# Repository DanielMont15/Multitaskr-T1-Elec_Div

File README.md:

## Multitaskr-T1-Elec_Div
# Electronics Division  
ECAD and documentation repository for everything electronics related to Rotational &amp; Controlled Mechanism and transmission system for camera scanner project.

# Abstract
Among the services offered by Multitaskr, a 3D manual scanning of rooms with a camera is performed. With the purpose of improving processes, the automation of this process is proposed by developing a mobile and foldable platform that allows modifying the Pitch and Yaw position (in a range of 360 and -45 to 45, respectively) of the camera via a robotic system with 2 degrees of freedom.

The development considers the use of SCRUM methodology to keep track of the proposed objectives and detected failures; CAD and ECAD software (SolidWorks and Eagle); MATLAB for the design and tuning of the controller; TEC laboratories and other related facilities; as well as testing the system to identify areas of opportunity.

In order to achieve this goal, the process will last 10 weeks and will be divided into areas (Mechanics, Electronics, Control and Manufacturing) with the involvement of 8th semester students in Mechatronics with relevant experience in these areas. The testing phase is intended to ensure the delivery of a product according to the specifications.  

A functional prototype is expected to be delivered with the requirements established in the design process; as well as an "Engineering Manual" with CAD models, research processes, schematics, codes and operation guidelines along with the tests and areas of opportunity identified. 

It has been identified that the system can improve the accuracy and efficiency of the process, benefiting Multitaskr operationally and providing its clients with greater value in the services acquired.

# Objective of this repository
To track and mantain in a single platform all related documents in order to be able to replicate the project if needed. Expect to find:
* Entries to the Engineering Manual on the electronics subdivision and updates to said entries.
* ECAD files of the desgined circuits
* Diagrams/Drawings

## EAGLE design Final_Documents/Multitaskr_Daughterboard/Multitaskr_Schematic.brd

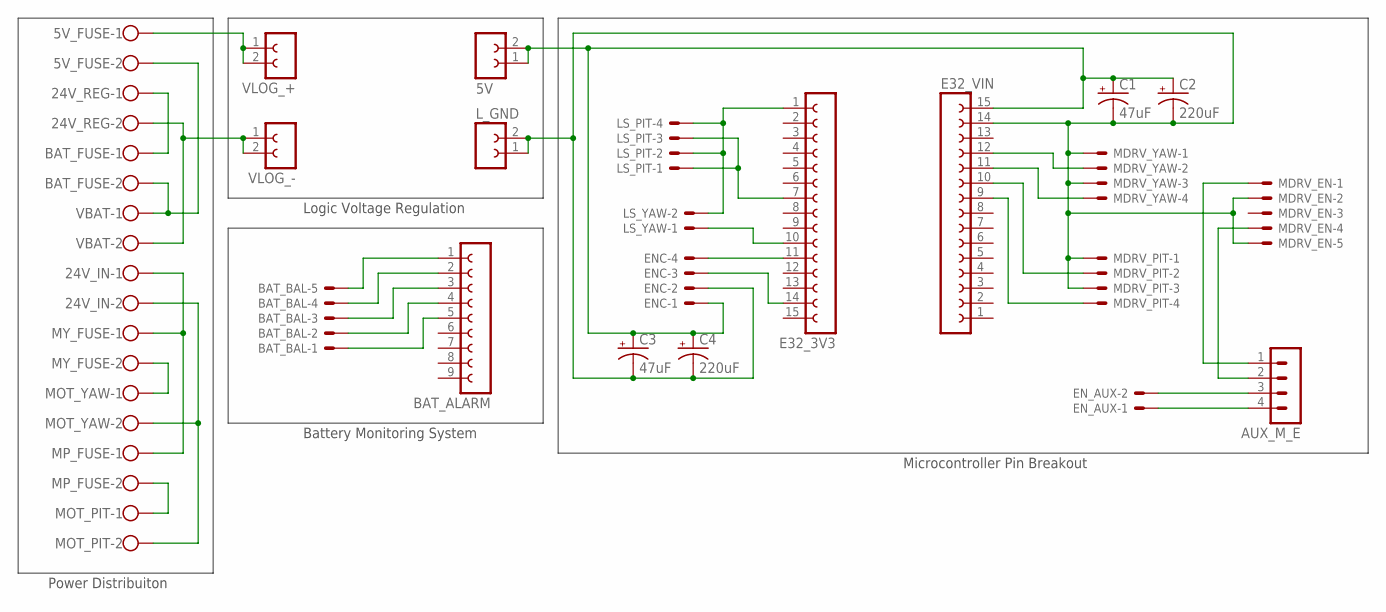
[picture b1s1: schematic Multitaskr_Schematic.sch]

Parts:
5V: FE05-1
5V_FUSE, 24V_IN, 24V_REG: SCREW_TERMINAL; FP_ST
AUX_M_E: MA04-1
BAT_ALARM: FE09-1; FE09
BAT_BAL: JST-XH-05-PIN-ROUND-PAD; JST-XH-05-PACKAGE-ROUND-PAD
BAT_FUSE: SCREW_TERMINAL; FP_ST
C1: 47uF; E2,5-7
C2: 220uF; E2,5RE
C3: 47uF; E2,5RE
C4: 220uF; E2,5-7
E32_3V3, E32_VIN: FE15-1; FE15
ENC: JST-XH-04-PIN-ROUND-PAD; JST-XH-04-PACKAGE-ROUND-PAD
EN_AUX: JST-XH-02-PIN-ROUND-PAD; JST-XH-02-PACKAGE-ROUND-PAD
LS_PIT: JST-XH-04-PIN-ROUND-PAD; JST-XH-04-PACKAGE-ROUND-PAD
LS_YAW: JST-XH-02-PIN-ROUND-PAD; JST-XH-02-PACKAGE-ROUND-PAD
L_GND: FE05-1
MDRV_EN: JST-XH-05-PIN-ROUND-PAD; JST-XH-05-PACKAGE-ROUND-PAD
MDRV_PIT: JST-XH-04-PIN-ROUND-PAD; JST-XH-04-PACKAGE-ROUND-PAD
MDRV_YAW: JST-XH-04-PIN-ROUND-PAD; JST-XH-04-PACKAGE-ROUND-PAD
MOT_PIT: SCREW_TERMINAL; FP_ST
MOT_YAW: SCREW_TERMINAL; FP_ST
MP_FUSE: SCREW_TERMINAL; FP_ST
MY_FUSE: SCREW_TERMINAL; FP_ST
VBAT: SCREW_TERMINAL; FP_ST
VLOG_+: FE05-1
VLOG_-: FE05-1

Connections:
1S: BAT_ALARM.2, BAT_BAL.4
2S: BAT_ALARM.3, BAT_BAL.3
3S: BAT_ALARM.4, BAT_BAL.2
3V3: E32_3V3.1, LS_PIT.2, LS_PIT.4, LS_YAW.2
4S: BAT_ALARM.5, BAT_BAL.1
5V: 5V.1, 5V.2, C1.+, C2.+, C3.+, C4.+, E32_VIN.15, ENC.1
24V: 24V_IN.1, MP_FUSE.1, MY_FUSE.1
-S: BAT_ALARM.1, BAT_BAL.5
BAT+: 5V_FUSE.2, BAT_FUSE.2, VBAT.1
BAT-: 24V_REG.2, VBAT.2, VLOG_-.1, VLOG_-.2
ENA_MOT_PIT: AUX_M_E.1, MDRV_EN.1
ENA_MOT_Y: AUX_M_E.2, MDRV_EN.4
EN_DIR: AUX_M_E.4, EN_AUX.1
EN_PGO: AUX_M_E.3, EN_AUX.2
ESP_SCL: E32_3V3.14, ENC.3
ESP_SDA: E32_3V3.11, ENC.4
FUSE_P: MOT_PIT.1, MP_FUSE.2
FUSE_REG: 24V_REG.1, BAT_FUSE.1
FUSE_Y: MOT_YAW.1, MY_FUSE.2
LS_PITCH: E32_3V3.7, LS_PIT.1, LS_PIT.3
LS_YAW: E32_3V3.10, LS_YAW.1
LV+: 5V_FUSE.1, VLOG_+.1, VLOG_+.2
L_GND: C1.-, C2.-, C3.-, C4.-, E32_VIN.14, ENC.2, L_GND.1, L_GND.2, MDRV_EN.2, MDRV_EN.5, MDRV_PIT.1, MDRV_PIT.3, MDRV_YAW.1, MDRV_YAW.3
M_GND: 24V_IN.2, MOT_PIT.2, MOT_YAW.2
PITCH_DIR: E32_VIN.10, MDRV_PIT.2
PITCH_PUL: E32_VIN.9, MDRV_PIT.4
YAW_DIR: E32_VIN.12, MDRV_YAW.2
YAW_PUL: E32_VIN.11, MDRV_YAW.4

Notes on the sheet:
Power Distribuiton
Logic Voltage Regulation
Battery Monitoring System
Microcontroller Pin Breakout

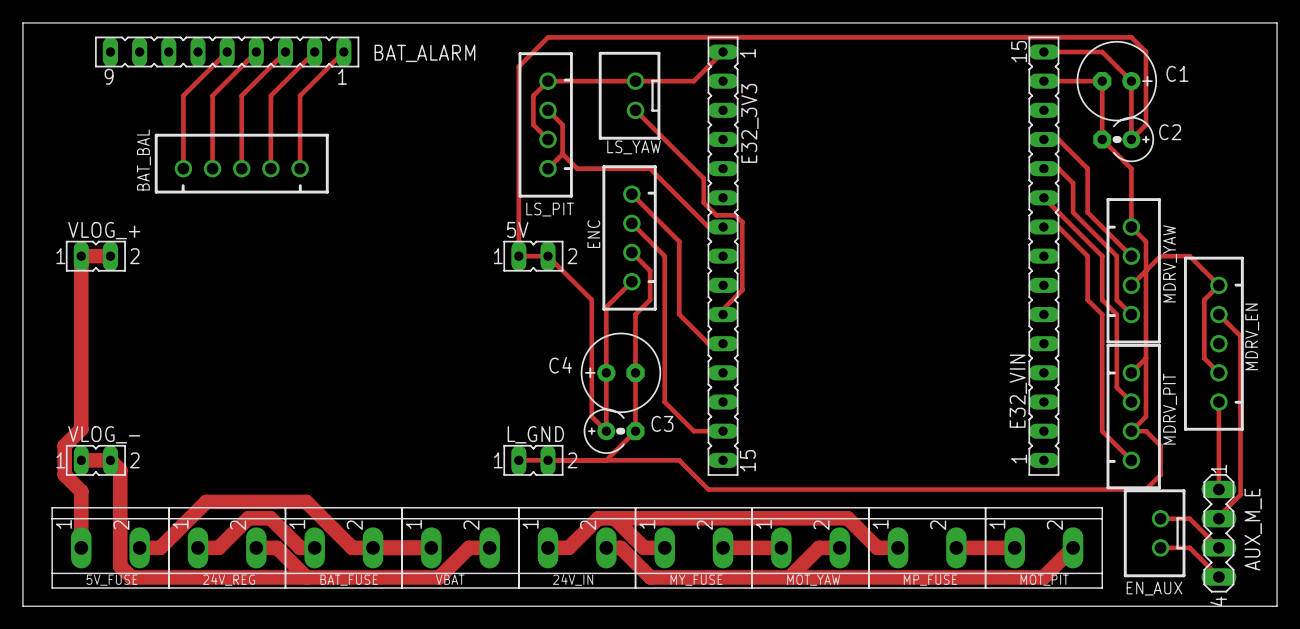
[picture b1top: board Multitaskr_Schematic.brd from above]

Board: 2 copper layers, 109.2 x 50.8 mm, 29 parts (0 on the bottom side), 28 nets.

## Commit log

2023-05-06 Updated README.md to describe project
2023-05-06 Added Log Books to git repository
2023-05-06 Added directory for Engineering Manual Entries
2023-05-06 Delete Engineering_Manual directory
    Fix Errors while uploading
2023-05-06 Created directory for Engineering entries; uploaded EM_ELEC-Selección_Fuente_Poder
2023-05-06 Added entry EM_ELEC-Selección_Microcontrolador
2023-05-06 Added first researchs documents of the project
2023-05-06 Added Actividad 2.1. Definición de objetivos, justificación y resultados esperados
2023-05-09 Fixed Table 3 Information to reflect consuption from 2 motors
2023-05-10 Added Power Supply Engineering Manual entry
2023-05-10 Added Battery Schematics
2023-05-10 Fixed typos
2023-05-11 Added guide document for battery selection to be sent to Multitaskr/Fixed typos in other documents
2023-05-11 Added Log Book 5
2023-05-13 Added entry for voltage regulators and motor control selection
2023-05-18 Updated file structure naming/Added General Electrical Schematics to work on main PCB
2023-05-24 Added first iteration of the PCB schematics; to be cleaned to improve readibility
2023-05-24 Added first iteration of daughterboard .brd file; to be redesigned to reflect current component sizes and layouts of current prototype board
2023-05-29 Added modified daughterboard schematic pdf
2023-05-29 Added updated .brd files of PCB (normal version and mirrored version)
2023-06-13 Updated Log documents and schematics
2023-06-13 Added Final Documents (IEEE Design report, EAGLE Project Files, Schematics and PCB Reference PDFs, Instruction Manual)
